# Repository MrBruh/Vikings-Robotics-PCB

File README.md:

A board with 2 ATMEGA microprocessors for controlling up to 7 DC motors and 4 servos

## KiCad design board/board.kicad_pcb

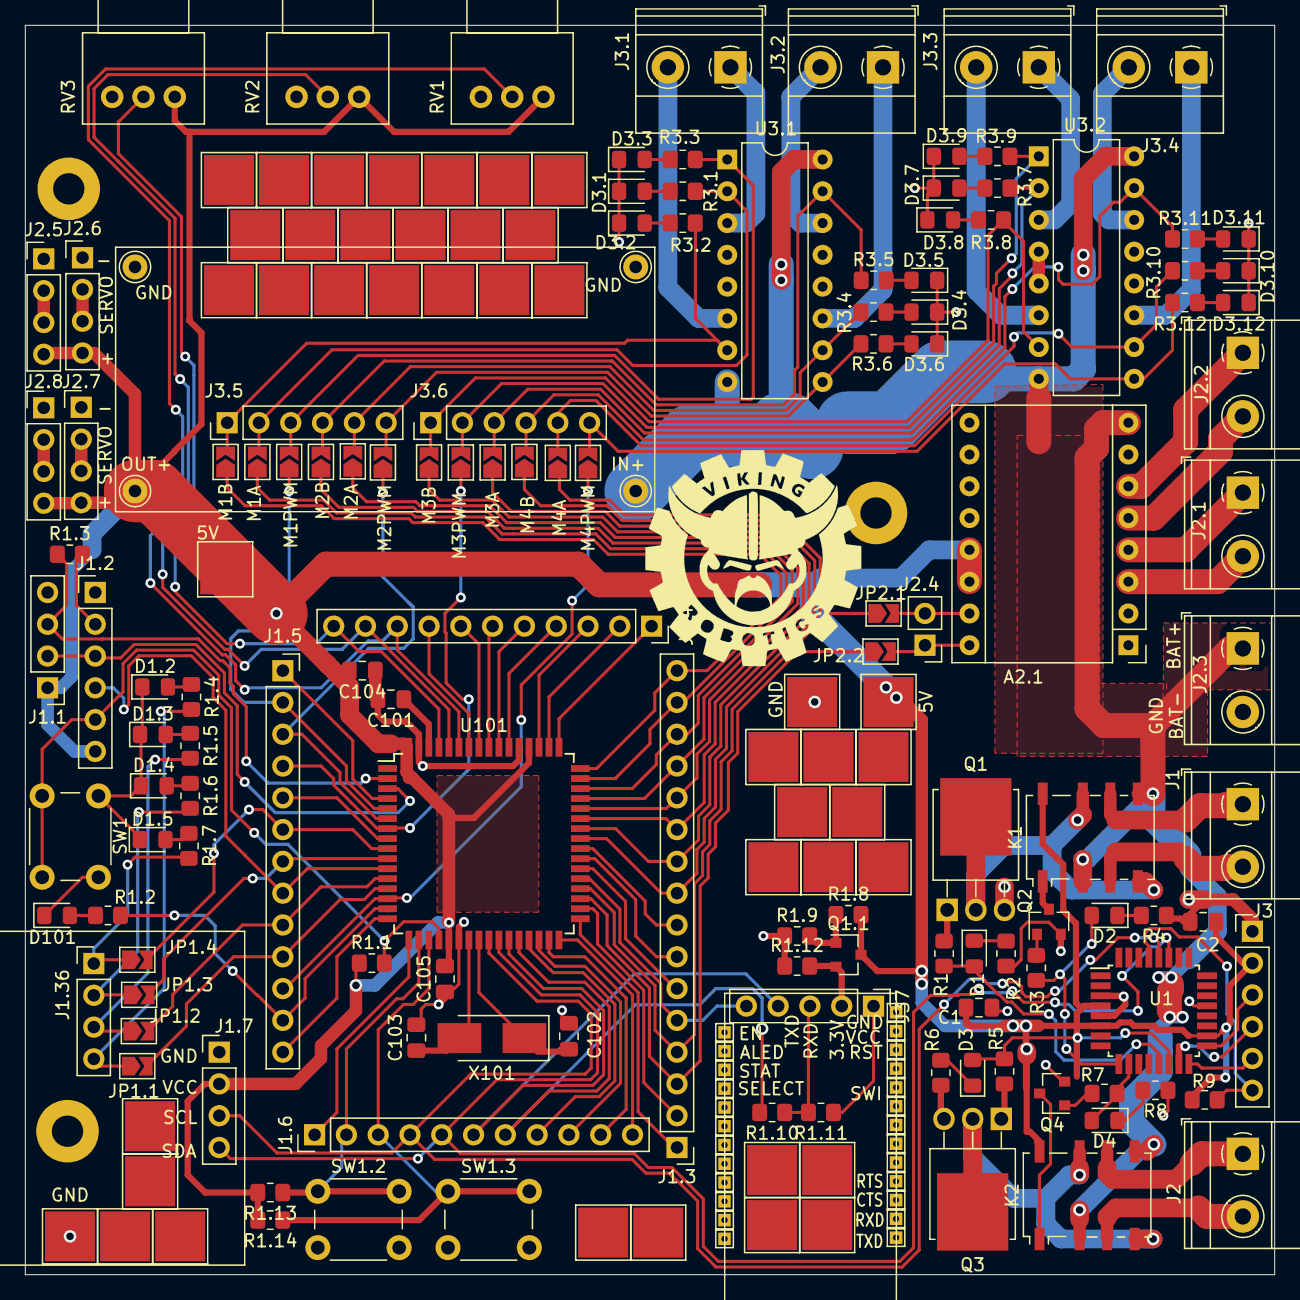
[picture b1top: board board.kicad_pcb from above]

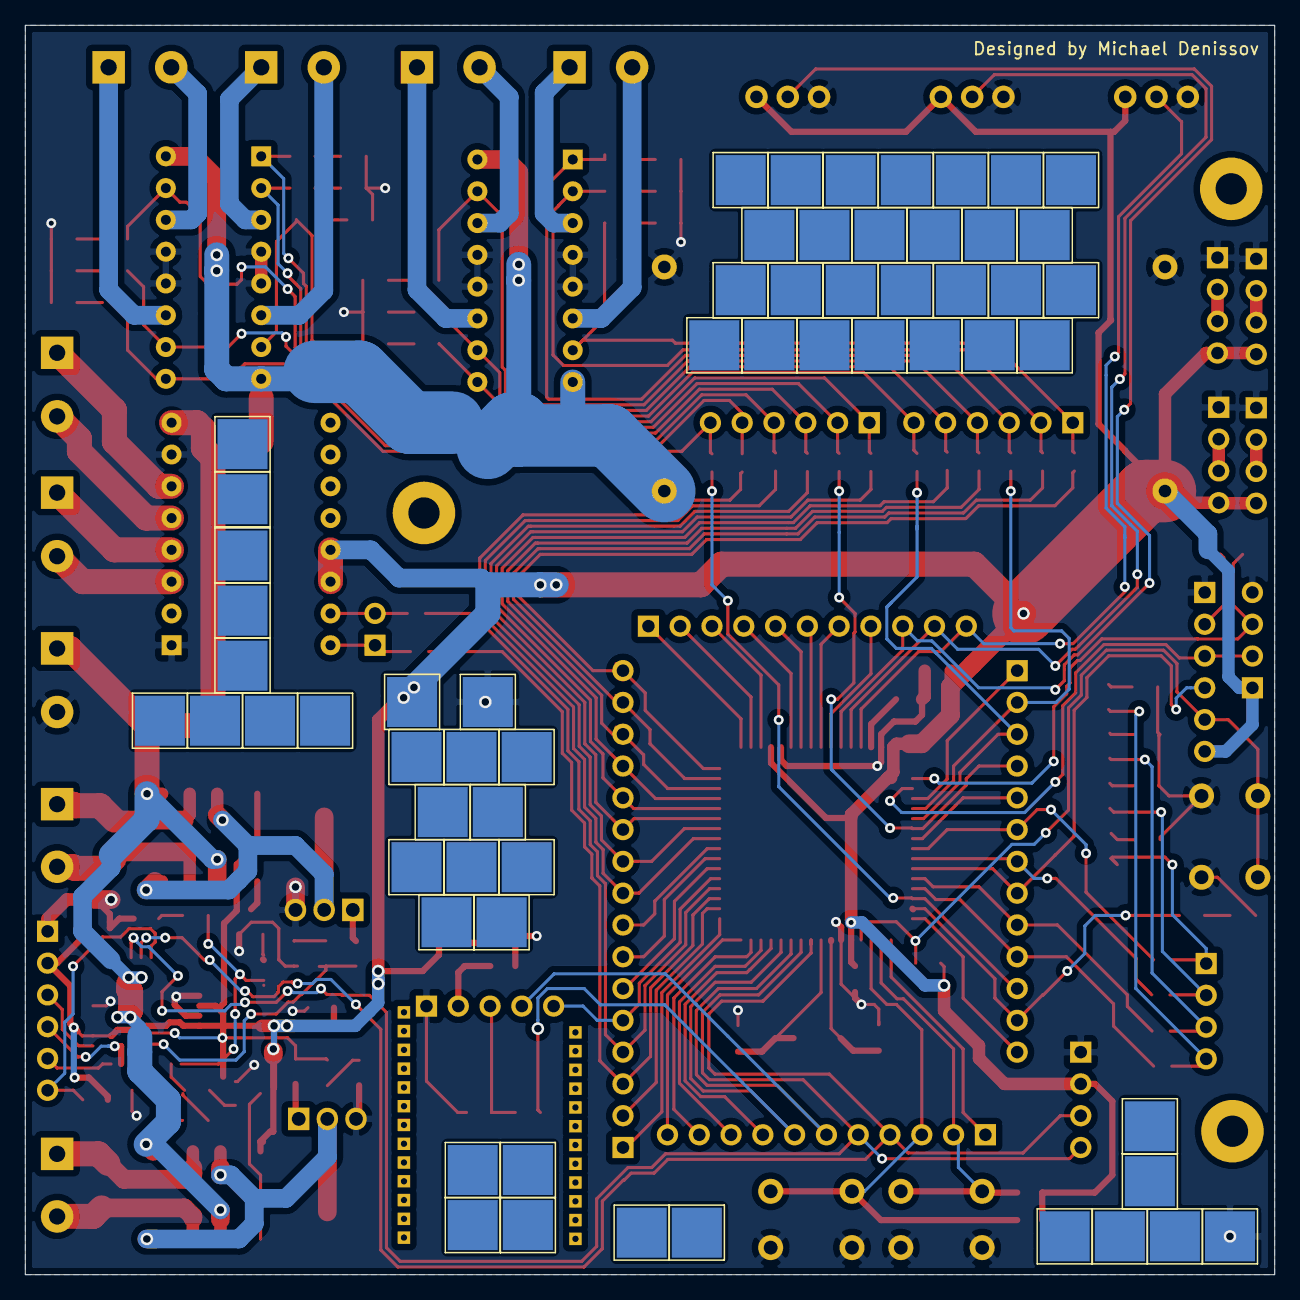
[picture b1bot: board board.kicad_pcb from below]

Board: 2 copper layers, 99.8 x 99.8 mm, 261 parts (60 on the bottom side), 139 nets.

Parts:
A2.1: Pololu_Breakout_DRV8825; Pololu_Breakout-16_15.2x20.3mm
C1, C2, C101, C102, C103, C104, C105: C; C_0805_2012Metric_Pad1.18x1.45mm_HandSolder
D1, D1.2, D1.3, D1.4, D1.5, D2, D3, D3.1, D3.2, D3.3, D3.4, D3.5, D3.6, D3.7, D3.8, D3.9, D3.10, D3.11, D3.12, D4, D101: LED; LED_0805_2012Metric_Pad1.15x1.40mm_HandSolder
H1, H4: GND; Pin_D1.0mm_L10.0mm
H2: IN+; Pin_D1.0mm_L10.0mm
H3: OUT+; Pin_D1.0mm_L10.0mm
H5, H6, H7: MountingHole; MountingHole_2.5mm_Pad
J1, J2, J3.1, J3.2, J3.3, J3.4: Conn_01x02; TerminalBlock_Phoenix_MKDS-1,5-2_1x02_P5.00mm_Horizontal
J1.1, J1.7, J1.36, J2.5, J2.6, J2.7, J2.8: Conn_01x04; PinHeader_1x04_P2.54mm_Vertical
J1.2, J3, J3.5, J3.6: Conn_01x06; PinHeader_1x06_P2.54mm_Vertical
J1.3: Conn_01x16; PinHeader_1x16_P2.54mm_Vertical
J1.4: Conn_01x11; PinSocket_1x11_P2.54mm_Vertical
J1.5: Conn_01x13; PinSocket_1x13_P2.54mm_Vertical
J1.6: Conn_01x11; PinHeader_1x11_P2.54mm_Vertical
J1.11: EN; TestPoint_THTPad_1.0x1.0mm_Drill0.5mm
J1.12: ALED; TestPoint_THTPad_1.0x1.0mm_Drill0.5mm
J1.13: STAT; TestPoint_THTPad_1.0x1.0mm_Drill0.5mm
J1.14: SELECT; TestPoint_THTPad_1.0x1.0mm_Drill0.5mm
J1.15, J1.16, J1.17, J1.18, J1.19, J1.20, J1.21, J1.22, J1.26, J1.28, J1.29, J1.30, J1.31: TestPoint_THTPad_1.0x1.0mm_Drill0.5mm
J1.23: GND; TestPoint_THTPad_1.0x1.0mm_Drill0.5mm
J1.24: VCC; TestPoint_THTPad_1.0x1.0mm_Drill0.5mm
J1.25: RST; TestPoint_THTPad_1.0x1.0mm_Drill0.5mm
J1.27: SWI; TestPoint_THTPad_1.0x1.0mm_Drill0.5mm
J1.32: RTS; TestPoint_THTPad_1.0x1.0mm_Drill0.5mm
J1.33: CTS; TestPoint_THTPad_1.0x1.0mm_Drill0.5mm
J1.34: RXD; TestPoint_THTPad_1.0x1.0mm_Drill0.5mm
J1.35: TXD; TestPoint_THTPad_1.0x1.0mm_Drill0.5mm
J2.1, J2.2, J2.3: Conn_01x02; TerminalBlock_Phoenix_MKDS-1,5-2-5.08_1x02_P5.08mm_Horizont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
J2.4: Conn_01x02; PinHeader_1x02_P2.54mm_Vertical
J37: Conn_01x05; PinHeader_1x05_P2.54mm_Vertical
JP1.1, JP1.2, JP1.3, JP1.4, JP3.11: M4PWM; SolderJumper-2_P1.3mm_Open_TrianglePad1.0x1.5mm
JP2.1, JP2.2: Jumper_2_Open; SolderJumper-2_P1.3mm_Open_TrianglePad1.0x1.5mm
JP3.5: M2PWM; SolderJumper-2_P1.3mm_Open_TrianglePad1.0x1.5mm
JP3.6: M2A; SolderJumper-2_P1.3mm_Open_TrianglePad1.0x1.5mm
JP3.7: M2B; SolderJumper-2_P1.3mm_Open_TrianglePad1.0x1.5mm
JP3.8: M1PWM; SolderJumper-2_P1.3mm_Open_TrianglePad1.0x1.5mm
JP3.9: M1A; SolderJumper-2_P1.3mm_Open_TrianglePad1.0x1.5mm
JP3.10: M1B; SolderJumper-2_P1.3mm_Open_TrianglePad1.0x1.5mm
JP3.12: M4A; SolderJumper-2_P1.3mm_Open_TrianglePad1.0x1.5mm
JP3.13: M4B; SolderJumper-2_P1.3mm_Open_TrianglePad1.0x1.5mm
JP3.14: M3A; SolderJumper-2_P1.3mm_Open_TrianglePad1.0x1.5mm
JP3.15: M3PWM; SolderJumper-2_P1.3mm_Open_TrianglePad1.0x1.5mm
JP3.16: M3B; SolderJumper-2_P1.3mm_Open_TrianglePad1.0x1.5mm
K1, K2: G6K-2; Relay_DPDT_Omron_G6K-2F-Y
Q1, Q3: IRLB8721PBF; TO-251-3-1EP_Horizontal_TabDown
Q1.1, Q2, Q4: AO3400A; SOT-23
R1, R3, R5, R7: 68; R_0805_2012Metric_Pad1.20x1.40mm_HandSolder
R1.1, R1.2, R1.3, R1.4, R1.5, R1.6, R1.7, R1.8, R1.9, R1.10, R1.11, R1.12, R1.13, R1.14: R; R_0805_2012Metric_Pad1.20x1.40mm_HandSolder
R2, R3.1, R3.2, R3.3, R3.4, R3.5, R3.6, R3.7, R3.8, R3.9, R3.10, R3.11, R3.12, R4, R6, R8: 200; R_0805_2012Metric_Pad1.20x1.40mm_HandSolder
R9: 10к; R_0805_2012Metric_Pad1.20x1.40mm_HandSolder
RV1, RV2, RV3: R_POT; Potentiometer_Alps_RK097_Single_Horizontal
SW1, SW1.2, SW1.3: SW_Push; SW_PUSH_6mm_H4.3mm
TP1, TP2, TP3, TP4, TP5, TP6, TP7, TP8, TP9, TP10, TP11, TP12, TP13, TP14, TP15, TP16, TP17, TP18, TP19, TP20, TP21, TP22, TP23, TP24, TP25, TP26, TP27, TP28, TP29, TP30, TP31, TP32, TP33, TP34, TP35, TP36, TP37, TP38, TP39, TP40, TP41, TP42, TP43, TP44, TP45, TP46, TP47, TP48, TP49, TP50, TP51, TP52, TP53, TP54, TP55, TP56, TP57, TP58, TP59, TP60, TP61, TP62, TP63, TP64, TP65, TP66, TP67, TP68, TP69, TP70, TP71, TP72, TP73, TP74, TP75, TP76, TP77, TP78, TP79, TP80, TP81, TP82, TP83, TP84, TP85, TP86, TP87, TP88, TP89, TP90, TP91, TP92, TP93, TP94, TP95, TP96, TP97, TP98, TP99, TP100, TP101, TP102: TestPoint; TestPoint_Pad_4.0x4.0mm
U1: ATmega8A-AU; TQFP-32_7x7mm_P0.8mm
U3.1, U3.2: L293D; DIP-16_W7.62mm
U99: viking
U101: ATmega128A-AU; TQFP-64_14x14mm_P0.8mm
X101: Crystal; Crystal_SMD_5032-2Pin_5.0x3.2mm_HandSoldering

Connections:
3.3V: J37.2, Q1.1.2, R1.12.2
5V: A2.1.13, A2.1.14, C1.1, C2.1, C104.2, C105.2, H3.1, J1.1.1, J1.2.6, J1.7.2, J2.5.4, J2.6.4, J2.7.4, J2.8.4, J3.2, K1.8, K2.8, Q1.1.3, R1.1.1, R1.8.2, R1.13.2, R1.14.2, R9.2, RV1.1, RV2.1, RV3.1, TP1.1, TP21.1, TP32.1, U1.4, U1.6, U1.18, U101.21, U101.52, U101.64
/MISO: J3.5, U1.16
/MOSI: J3.4, U1.15
/RST: J3.6, R9.1, U1.29
/SCK: J3.3, U1.17
/atmega128/PDI: J1.2.2, R1.3.2
/atmega128/PDO: J1.1.2, J1.2.3, U101.3
/atmega128/RESET: J1.2.5, R1.1.2, SW1.2, U101.20
/atmega128/TX: J1.1.3, R1.3.1, U101.2
B_RXD: J1.6.7, R1.10.2, U101.28
B_STAT: J1.3.5, J37.5, U101.37
B_TXD: J1.6.6, J37.4, U101.27
GND: A2.1.1, A2.1.7, C1.2, C2.2, C101.2, C102.2, C103.2, C104.1, C105.1, D1.2.1, D1.3.1, D1.4.1, D1.5.1, D3.1.1, D3.2.1, D3.3.1, D3.4.1, D3.5.1, D3.6.1, D3.7.1, D3.8.1, D3.9.1, D3.10.1, D3.11.1, D3.12.1, D101.1, H1.1, H4.1, J1.1.4, J1.2.1, J1.7.1, J2.3.2, J2.5.1, J2.6.1, J2.7.1, J2.8.1, J3.1, J37.1, Q1.3, Q2.2, Q3.3, Q4.2, R1.9.1, R1.11.1, R1.12.1, R2.1, R4.1, R6.1, R8.1, RV1.3, RV2.3, RV3.3, SW1.1, SW1.2.2, SW1.3.2, TP2.1, TP27.1, TP92.1, TP97.1, U1.3, U1.5, U1.21, U3.1.4, U3.1.5, U3.1.12, U3.1.13, U3.2.4, U3.2.5, U3.2.12, U3.2.13, U101.22, U101.53, U101.63
M1A: J1.3.15, JP3.9.1, U101.47
M1B: J1.3.16, JP3.10.1, U101.48
M1PWM: J1.5.2, JP3.8.1, U101.5
M2A: J1.3.13, JP3.6.1, U101.45
M2B: J1.3.14, JP3.7.1, U101.46
M2PWM: J1.5.3, JP3.5.1, U101.6
M3A: J1.3.11, JP3.14.1, U101.43
M3B: J1.3.12, JP3.16.1, U101.44
M3PWM: J1.5.4, JP3.15.1, U101.7
M4A: J1.3.9, JP3.12.1, U101.41
M4B: J1.3.10, JP3.13.1, U101.42
M4PWM: J1.5.11, JP3.11.1, U101.14
unnamed: A2.1.3, J2.1.2
unnamed: A2.1.4, J2.1.1
unnamed: A2.1.5, J2.2.2
unnamed: A2.1.6, J2.2.1
unnamed: A2.1.15, J2.4.2, JP2.1.2
unnamed: A2.1.16, J2.4.1, JP2.2.2
unnamed: C101.1, U101.62
unnamed: C102.1, U101.24, X101.1
unnamed: C103.1, U101.23, X101.2
unnamed: D1.1, R2.2
unnamed: D1.2, R1.2, U1.13
unnamed: D1.2.2, R1.4.1
unnamed: D1.3.2, R1.5.1
unnamed: D1.4.2, R1.6.1
unnamed: D1.5.2, R1.7.1
unnamed: D2.1, R4.2
unnamed: D2.2, R3.2, U1.9
unnamed: D3.1, R6.2
unnamed: D3.2, R5.2, U1.14
unnamed: D3.1.2, R3.1.2
unnamed: D3.2.2, R3.2.2
unnamed: D3.3.2, R3.3.2
unnamed: D3.4.2, R3.4.2
unnamed: D3.5.2, R3.5.2
unnamed: D3.6.2, R3.6.2
unnamed: D3.7.2, R3.7.2
unnamed: D3.8.2, R3.8.2
unnamed: D3.9.2, R3.9.2
unnamed: D3.10.2, R3.10.2
unnamed: D3.11.2, R3.11.2
unnamed: D3.12.2, R3.12.2
unnamed: D4.1, R8.2
unnamed: D4.2, R7.2, U1.10
unnamed: D101.2, R1.2.1
unnamed: J1.1, K1.6
unnamed: J1.2, K1.3
unnamed: J1.36.1, JP1.4.1, R1.7.2
unnamed: J1.36.2, JP1.3.1, R1.6.2
unnamed: J1.36.3, JP1.2.1, R1.5.2
unnamed: J1.36.4, JP1.1.1, R1.4.2
unnamed: J2.1, K2.6
unnamed: J2.2, K2.3
unnamed: J2.5.2, J2.5.3
unnamed: J2.6.2, J2.6.3
unnamed: J2.7.2, J2.7.3
unnamed: J2.8.2, J2.8.3
unnamed: J3.1.1, U3.1.3
unnamed: J3.1.2, U3.1.6
unnamed: J3.2.1, U3.1.11
unnamed: J3.2.2, U3.1.14
unnamed: J3.3.1, U3.2.3
unnamed: J3.3.2, U3.2.6
unnamed: J3.4.1, U3.2.11
unnamed: J3.4.2, U3.2.14
unnamed: J3.5.1, JP3.10.2, R3.2.1, U3.1.7
unnamed: J3.5.2, JP3.9.2, R3.1.1, U3.1.2
unnamed: J3.5.3, JP3.8.2, R3.3.1, U3.1.1
unnamed: J3.5.4, JP3.7.2, R3.5.1, U3.1.15
unnamed: J3.5.5, JP3.6.2, R3.4.1, U3.1.10
unnamed: J3.5.6, JP3.5.2, R3.6.1, U3.1.9
unnamed: J3.6.1, JP3.16.2, R3.8.1, U3.2.7
unnamed: J3.6.2, JP3.15.2, R3.9.1, U3.2.1
unnamed: J3.6.3, JP3.14.2, R3.7.1, U3.2.2
unnamed: J3.6.4, JP3.13.2, R3.11.1, U3.2.15
unnamed: J3.6.5, JP3.12.2, R3.10.1, U3.2.10
unnamed: J3.6.6, JP3.11.2, R3.12.1, U3.2.9
unnamed: J37.3, R1.10.1, R1.11.2
unnamed: K1.1, Q2.3
unnamed: K1.4, K1.7, Q1.2
unnamed: K2.1, Q4.3
unnamed: K2.4, K2.7, Q3.2
unnamed: Q1.1, R1.1
unnamed: Q1.1.1, R1.8.1, R1.9.2
unnamed: Q2.1, R3.1
unnamed: Q3.1, R5.1
unnamed: Q4.1, R7.1
PA0: J1.4.3, U101.51
PA1: J1.4.2, U101.50
PA2: J1.4.1, U101.49
PB0: J1.5.7, JP1.3.2, U101.10
PB1: J1.2.4, J1.5.8, U101.11
PB2: J1.5.9, JP1.2.2, U101.12
PB3: J1.5.10, JP1.1.2, U101.13
PB5: J1.5.12, R1.2.2, U101.15
PB6: J1.5.13, U101.16
PB7: J1.6.1, U101.17
PC0: J1.3.3, JP2.2.1, U101.35
PC1: J1.3.4, JP2.1.1, U101.36
PC3: J1.3.6, U101.38
PC4: J1.3.7, U101.39
PC5: J1.3.8, U101.40
PD0: J1.6.4, J1.7.3, U1.28, U101.25
PD1: J1.6.5, J1.7.4, U1.27, U101.26
PD4: J1.6.8, U101.29
PD5: J1.6.9, U101.30
PD6: J1.6.10, U101.31
PD7: J1.6.11, U101.32
PE2: J1.5.1, U101.4
PE6: J1.5.5, U101.8
PE7: J1.5.6, JP1.4.2, U101.9
PF0: J1.4.11, RV3.2, U101.61
PF1: J1.4.10, RV2.2, U101.60
PF2: J1.4.9, RV1.2, U101.59
PF3: J1.4.8, U101.58
PF4: J1.4.7, U101.57
PF5: J1.4.6, U101.56
PF6: J1.4.5, U101.55
PF7: J1.4.4, U101.54
PG0: J1.3.1, U101.33
PG1: J1.3.2, U101.34
PG3: J1.6.2, R1.13.1, SW1.2.1, U101.18
PG4: J1.6.3, R1.14.1, SW1.3.1, U101.19
V_MOT: A2.1.8, H2.1, J2.3.1, K1.2, K1.5, K2.2, K2.5, U3.1.8, U3.1.16, U3.2.8, U3.2.16

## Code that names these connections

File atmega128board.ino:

// Motors
#include<Wire.h>

#define LED1 11
#define LED2 10
#define LED3 8
#define LED4 7

#define M1PWM 3
#define M2PWM 4
#define M3PWM 5

#define M1B 41
#define M1A 40
#define M2B 39
#define M2A 38
#define M3B 37

#define M3A 36

#define M4PWM 12
#define M4A   34
#define M4B   35

void transmit(char command, int motor, int value = 0);

int x = 20;

void setup() {
  Wire.begin(); // join i2c bus (address optional for master)
  pinMode(LED1, OUTPUT);
  pinMode(LED2, OUTPUT);
  pinMode(LED3, OUTPUT);
  pinMode(LED4, OUTPUT);

  pinMode(M1PWM, OUTPUT);
  pinMode(M1A, OUTPUT);
  pinMode(M1B, OUTPUT);

  pinMode(M2PWM, OUTPUT);
  pinMode(M2A, OUTPUT);
  pinMode(M2B, OUTPUT);

  pinMode(M3PWM, OUTPUT);
  pinMode(M3A, OUTPUT);
  pinMode(M3B, OUTPUT);

  pinMode(M4PWM, OUTPUT);
  pinMode(M4A, OUTPUT);
  pinMode(M4B, OUTPUT);

  Serial1.begin(9600);
  pinMode(LED_BUILTIN, OUTPUT);

}
int incomingByte = 0;    // for incoming serial data

int waiting = 1000;

void loop() {
  transmit('R', 1, 100);
  digitalWrite(LED1, HIGH);
  writeL1(LOW, HIGH, 100, HIGH, LOW, 100);
  writeL2(LOW, HIGH, 100, HIGH, LOW, 100);
  checkSerial();
  delay(waiting);
  
  transmit('F', 2, 100);
  digitalWrite(LED2, HIGH);
  checkSerial();
  delay(waiting);
 
  digitalWrite(LED3, HIGH);
  transmit('R', 2, 100);
  writeL1(HIGH, LOW, 100, LOW, HIGH, 100);
  writeL2(HIGH, LOW, 100, LOW, HIGH, 100);
  checkSerial();
  delay(waiting);

  digitalWrite(LED4, HIGH);
  transmit('F', 2, 100);
  checkSerial();
  delay(waiting);

  digitalWrite(LED1, LOW);
  transmit('R', 1, 0);
  writeL1(LOW, HIGH, 100, HIGH, LOW, 100);
  writeL2(LOW, HIGH, 100, HIGH, LOW, 100);
  checkSerial();
  delay(waiting);

  digitalWrite(LED2, LOW);
  transmit('F', 1, 100);
  checkSerial();
  delay(waiting);

  digitalWrite(LED3, LOW);
  transmit('S', 2);
  writeL1(HIGH, LOW, 100, LOW, HIGH, 100);
  writeL2(HIGH, LOW, 100, LOW, HIGH, 100);
  checkSerial();
  delay(waiting);

  digitalWrite(LED4, LOW);
  transmit('B', 1);
  checkSerial();
  delay(waiting);
 
}

void transmit(char command, int motor, int value) {
  int sync = 255;
  Wire.beginTransmission(8); // transmit to device #8
  Wire.write(sync);
  Wire.write(command);
  Wire.write(motor);
  Wire.write(value);              // sends one byte
  Wire.endTransmission();    // stop transmitting
}

void writeL1(int a1, int b1, int pwm1, int a2, int b2, int pwm2) {
  digitalWrite(M1A, a1);
  digitalWrite(M1B, b1);
  analogWrite(M1PWM, pwm1);
  digitalWrite(M2A, a2);
  digitalWrite(M2B, b2);
  analogWrite(M2PWM, pwm2);
}

void writeL2(int a3, int b3, int pwm3, int a4, int b4, int pwm4) {
  digitalWrite(M3A, a3);
  digitalWrite(M3B, b3);
  analogWrite(M3PWM, pwm3);
  digitalWrite(M4A, a4);
  digitalWrite(M4B, b4);
  analogWrite(M4PWM, pwm4);
}
int mode = LOW;

void checkSerial() {
  if (Serial1.available() > 0) {
  
    // read the incoming byte:
    incomingByte = Serial1.read();
  
    // say what you got:
    Serial1.print((char)incomingByte);
    if(mode == LOW) {
      mode = HIGH;
    } else if(mode == HIGH) {
      mode = LOW;
    }
    pinMode(LED_BUILTIN, mode);
  }
}

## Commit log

2020-11-07 uploaded updated pcb design
2020-11-11 updated pcb design
